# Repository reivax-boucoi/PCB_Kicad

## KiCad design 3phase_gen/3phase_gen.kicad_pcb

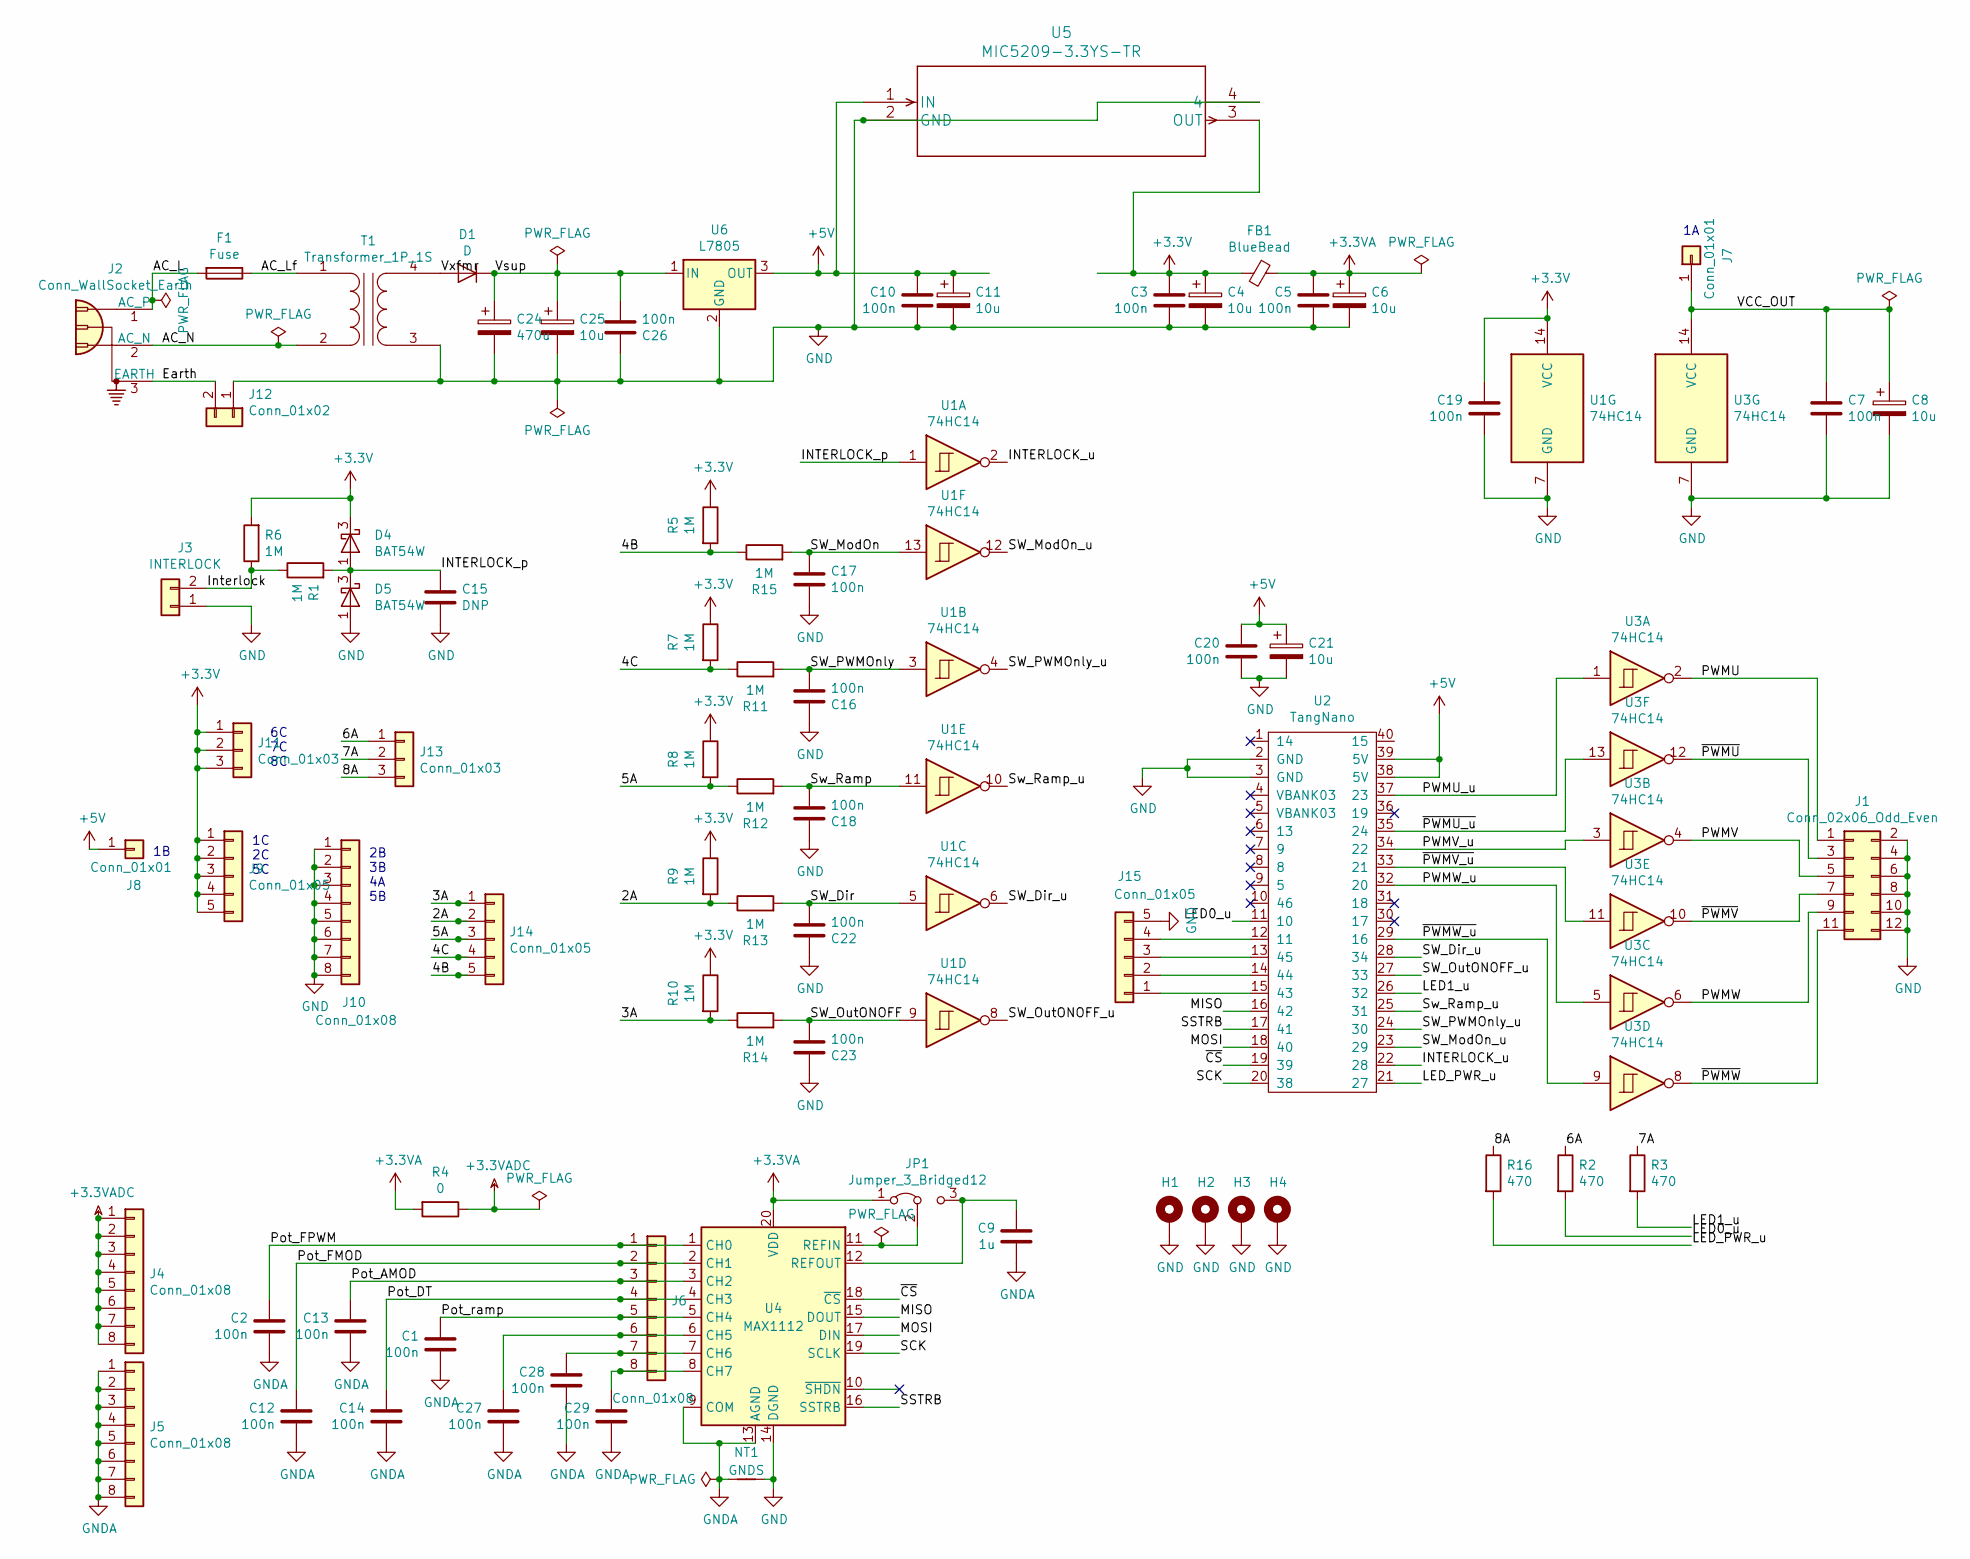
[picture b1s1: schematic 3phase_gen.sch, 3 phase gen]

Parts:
C1, C2, C3, C5, C7, C10, C12, C13, C14, C16, C17, C18, C19, C20, C22, C23, C26, C27, C28, C29: 100n; C_0805_2012Metric_Pad1.15x1.40mm_HandSolder
C4, C6, C8, C11, C21, C25: 10u; CP_Radial_D5.0mm_P2.50mm
C9: 1u; C_0805_2012Metric_Pad1.15x1.40mm_HandSolder
C15: DNP; C_0805_2012Metric_Pad1.15x1.40mm_HandSolder
C24: 470u; CP_Radial_D10.0mm_P5.00mm
D1: D; D_DO-15_P12.70mm_Horizontal
D4, D5: BAT54W; SOT-323_SC-70
F1: Fuse; Fuseholder_Cylinder-5x20mm_Stelvio-Kontek_PTF78_Horizontal_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
FB1: BlueBead; FerriteBead
H1, H2, H3, H4: MountingHole_Pad; MountingHole_3.2mm_M3_Pad
J1: Conn_02x06_Odd_Even; PinHeader_2x06_P2.54mm_Horizontal
J2: Conn_WallSocket_Earth; IEC_mains_3pin
J3: INTERLOCK; SolderWirePad_1x02_P3.81mm_Drill1.2mm
J4, J5, J6, J10: Conn_01x08; PinHeader_1x08_P2.54mm_Vertical
J7, J8: Conn_01x01; PinHeader_1x01_P2.54mm_Vertical
J9, J14, J15: Conn_01x05; PinHeader_1x05_P2.54mm_Vertical
J11, J13: Conn_01x03; PinHeader_1x03_P2.54mm_Vertical
J12: Conn_01x02; PinHeader_1x02_P2.54mm_Vertical
JP1: Jumper_3_Bridged12; SolderJumper-3_P1.3mm_Bridged12_RoundedPad1.0x1.5mm
NT1: GNDS; NetTie-2_SMD_Pad0.5mm
R1, R11, R12, R13, R14, R15: 1M; R_Axial_DIN0207_L6.3mm_D2.5mm_P10.16mm_Horizontal
R2, R3, R16: 470; R_0805_2012Metric_Pad1.15x1.40mm_HandSolder
R4: 0; R_Axial_DIN0207_L6.3mm_D2.5mm_P10.16mm_Horizontal
R5, R6, R7, R8, R9, R10: 1M; R_0805_2012Metric_Pad1.15x1.40mm_HandSolder
T1: Transformer_1P_1S; VB1-2-1-12_transformer
U1, U3: 74HC14; DIP-14_W7.62mm_LongPads
U2: TangNano
U4: MAX1112; SSOP-20_5.3x7.2mm_P0.65mm
U5: MIC5209-3.3YS-TR; SOT-223
U6: L7805; TO-220F-3_Vertical

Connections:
+3.3VA: C5.2, C6.1, FB1.1, JP1.1 (A), R4.2, U4.20 (VDD)
+3.3VADC: J4.1, J4.2, J4.3, J4.4, J4.5, J4.6, J4.7, J4.8, R4.1
+3V3: C3.2, C4.1, C19.2, D4.3 (K), FB1.2, J9.1, J9.2, J9.3, J9.4, J9.5, J11.1, J11.2, J11.3, R5.1, R6.2, R7.1, R8.1, R9.1, R10.1, U1.14 (VCC), U5.3 (OUT)
+5V: C10.2, C11.1, C20.2, C21.1, J8.1, U2.38 (5V), U2.39 (5V), U5.1 (IN), U6.3 (OUT)
/2A: J14.2, R9.2, R13.1
/3A: J14.1, R10.2, R14.1
/4B: J14.5, R5.2, R15.1
/4C: J14.4, R7.2, R11.1
/5A: J14.3, R8.2, R12.1
/6A: J13.1, R2.1
/7A: J13.2, R3.1
/8A: J13.3, R16.1
/AC_L: F1.2, J2.1 (AC_P)
/AC_Lf: F1.1, T1.1 (AA)
/AC_N: J2.2 (AC_N), T1.2 (AB)
/Earth: J2.3 (EARTH), J12.2
/INTERLOCK_p: C15.2, D4.1 (A), D5.3 (K), R1.2, U1.1
/INTERLOCK_u: U1.2, U2.22 (28)
/Interlock: J3.2, R1.1, R6.1
/LED0_u: R2.2, U2.11 (10)
/LED1_u: R3.2, U2.26 (32)
/LED_PWR_u: R16.2, U2.21 (27)
/MISO: U2.16 (42), U4.15 (DOUT)
/MOSI: U2.18 (40), U4.17 (DIN)
/PWMU: J1.1, U3.2
/PWMU_u: U2.37 (23), U3.1
/PWMV: J1.5, U3.4
/PWMV_u: U2.34 (22), U3.3
/PWMW: J1.9, U3.6
/PWMW_u: U2.32 (20), U3.5
/Pot_AMOD: C13.2, J6.3, U4.3 (CH2)
/Pot_DT: C14.2, J6.4, U4.4 (CH3)
/Pot_FMOD: C12.2, J6.2, U4.2 (CH1)
/Pot_FPWM: C2.2, J6.1, U4.1 (CH0)
/Pot_ramp: C1.2, J6.5, U4.5 (CH4)
/SCK: U2.20 (38), U4.19 (SCLK)
/SSTRB: U2.17 (41), U4.16 (SSTRB)
/SW_Dir: C22.1, R13.2, U1.5
/SW_Dir_u: U1.6, U2.28 (34)
/SW_ModOn: C17.2, R15.2, U1.13
/SW_ModOn_u: U1.12, U2.23 (29)
/SW_OutONOFF: C23.1, R14.2, U1.9
/SW_OutONOFF_u: U1.8, U2.27 (33)
/SW_PWMOnly: C16.1, R11.2, U1.3
/SW_PWMOnly_u: U1.4, U2.24 (30)
/Sw_Ramp: C18.1, R12.2, U1.11
/Sw_Ramp_u: U1.10, U2.25 (31)
/VCC_OUT: C7.1, C8.1, J7.1, U3.14 (VCC)
/Vsup: C24.1, C25.1, C26.1, D1.1 (K), U6.1 (IN)
/Vxfmr: D1.2 (A), T1.4 (SB)
/~CS: U2.19 (39), U4.18 (~CS)
/~PWMU: J1.3, U3.12
/~PWMU_u: U2.35 (24), U3.13
/~PWMV: J1.7, U3.10
/~PWMV_u: U2.33 (21), U3.11
/~PWMW: J1.11, U3.8
/~PWMW_u: U2.29 (16), U3.9
GND: C3.1, C4.2, C5.1, C6.2, C7.2, C8.2, C10.1, C11.2, C15.1, C16.2, C17.1, C18.2, C19.1, C20.1, C21.2, C22.2, C23.2, C24.2, C25.2, C26.2, D5.1 (A), H1.1, H2.1, H3.1, H4.1, J1.2, J1.4, J1.6, J1.8, J1.10, J1.12, J3.1, J10.1, J10.2, J10.3, J10.4, J10.5, J10.6, J10.7, J10.8, J12.1, J15.5, NT1.2, T1.3 (SA), U1.7 (GND), U2.2 (GND), U2.3 (GND), U3.7 (GND), U4.14 (DGND), U5.2 (GND), U5.4, U6.2 (GND)
GNDA: C1.1, C2.1, C9.1, C12.1, C13.1, C14.1, C27.1, C28.1, C29.1, J5.1, J5.2, J5.3, J5.4, J5.5, J5.6, J5.7, J5.8, NT1.1, U4.9 (COM), U4.13 (AGND)
unnamed: C9.2, JP1.3 (B), U4.12 (REFOUT)
unnamed: C27.2, J6.6, U4.6 (CH5)
unnamed: C28.2, J6.7, U4.7 (CH6)
unnamed: C29.2, J6.8, U4.8 (CH7)
unnamed: J15.1, U2.15 (43)
unnamed: J15.2, U2.14 (44)
unnamed: J15.3, U2.13 (45)
unnamed: J15.4, U2.12 (11)
unnamed: JP1.2 (C), U4.11 (REFIN)

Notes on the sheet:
1C 2C 5C
2B 3B 4A 5B
6C 7C 8C

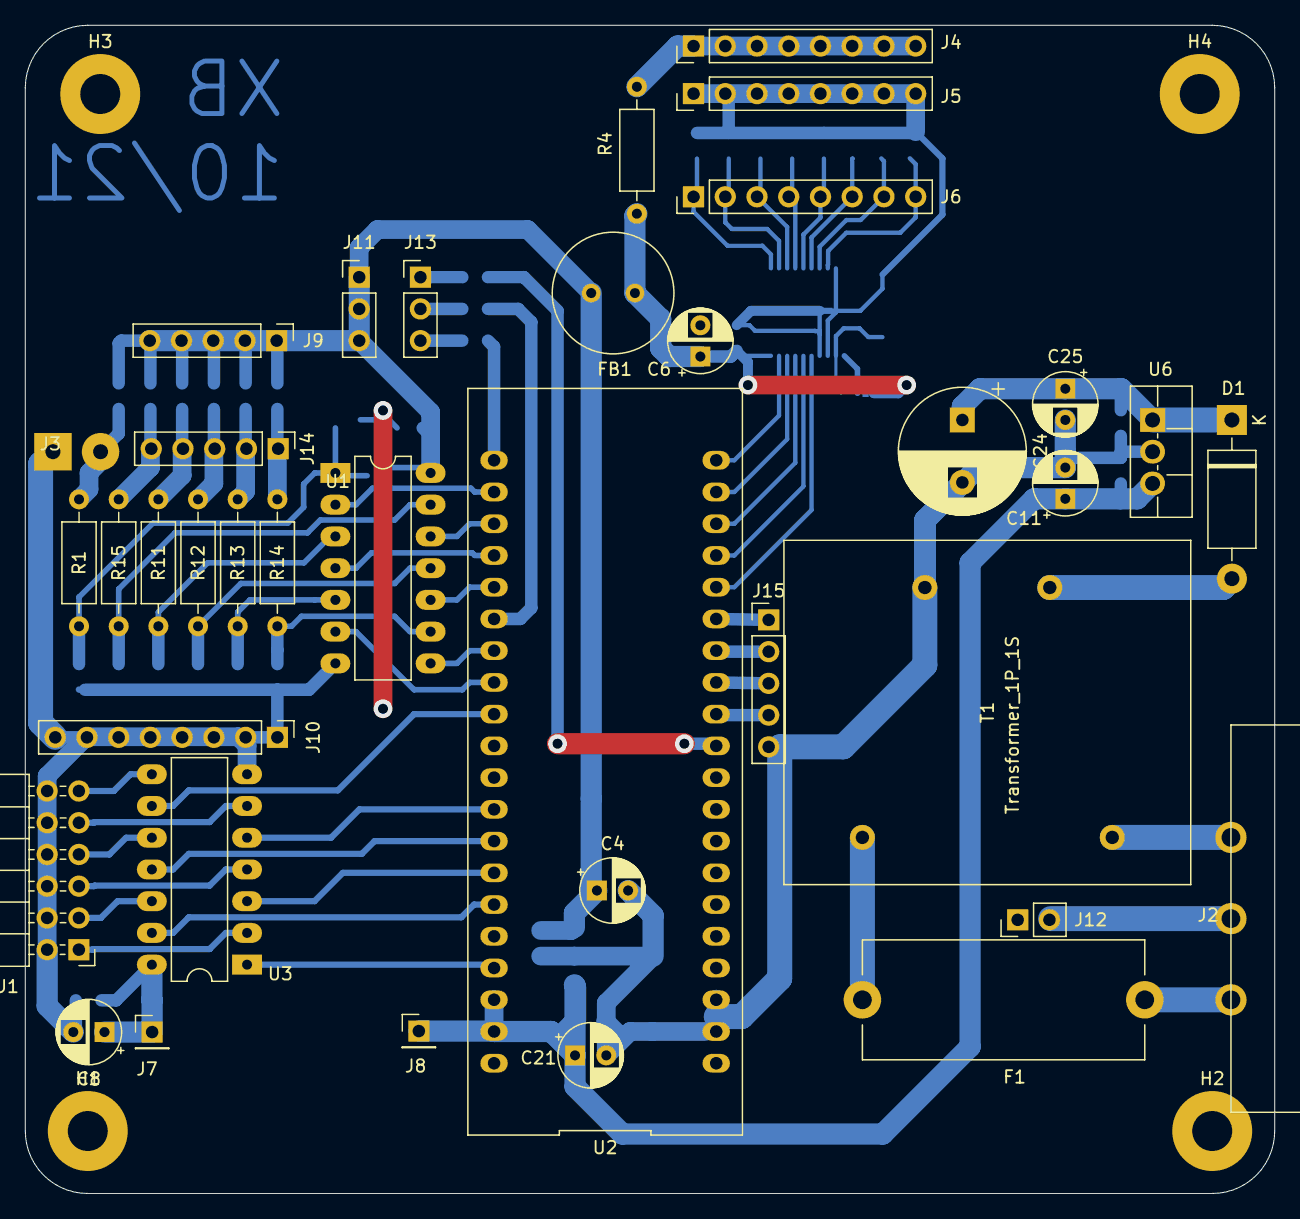
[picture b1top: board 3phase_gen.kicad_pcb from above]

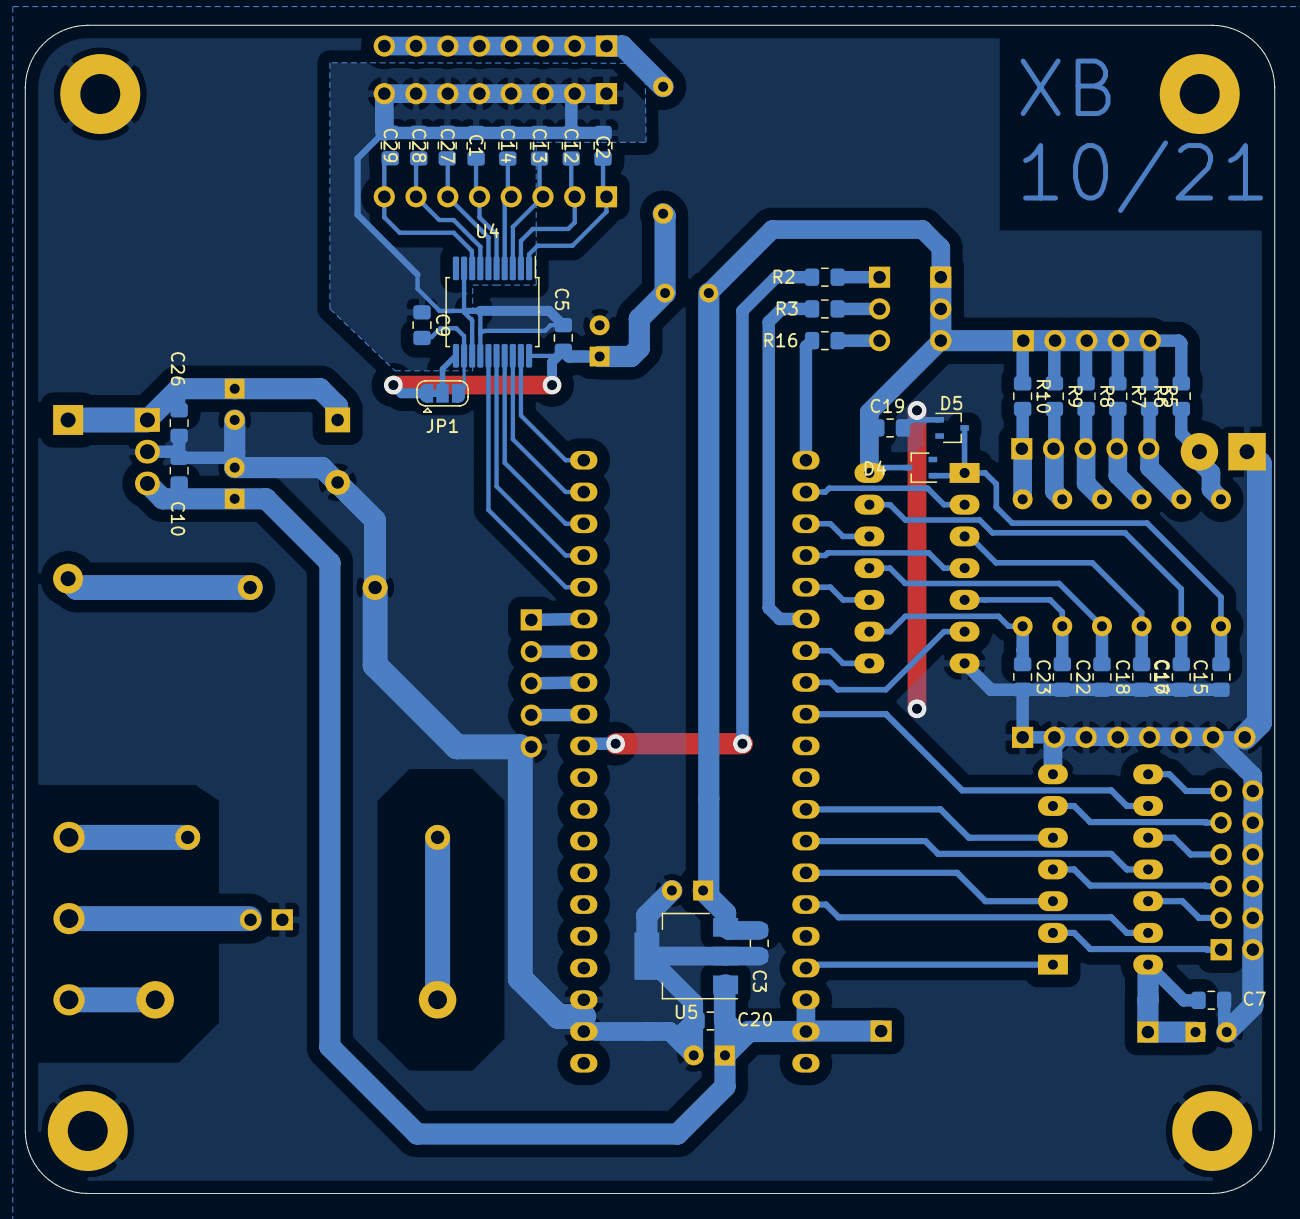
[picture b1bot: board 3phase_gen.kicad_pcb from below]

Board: 2 copper layers, 100.0 x 93.5 mm, 78 parts (37 on the bottom side), 68 nets.

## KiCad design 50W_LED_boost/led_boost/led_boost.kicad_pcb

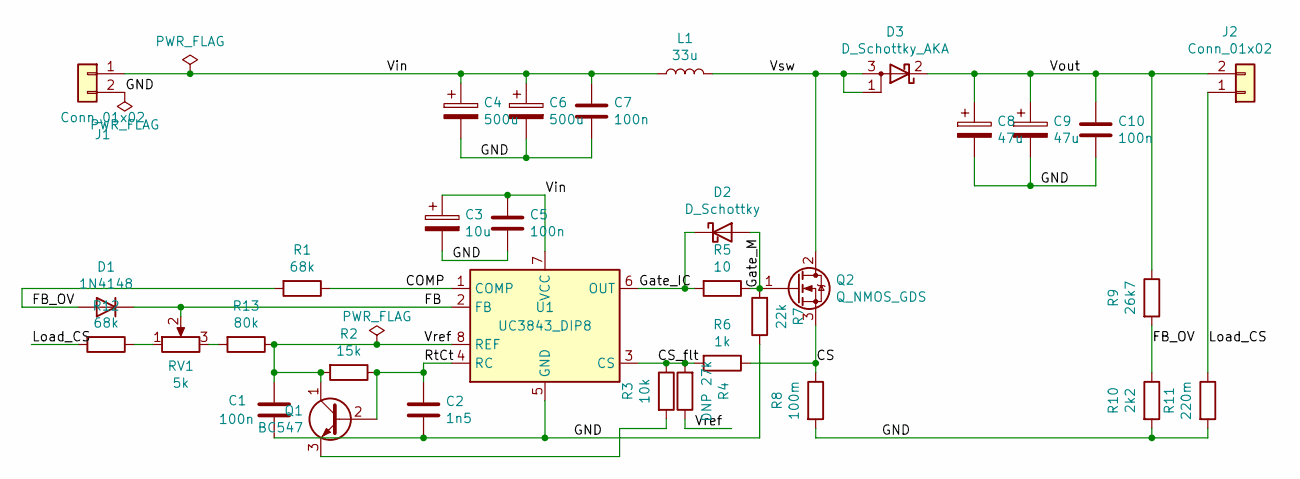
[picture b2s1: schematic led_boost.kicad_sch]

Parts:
C1, C5, C7, C10: 100n; C_Disc_D5.0mm_W2.5mm_P5.00mm
C2: 1n5; C_Disc_D5.0mm_W2.5mm_P5.00mm
C3: 10u; CP_Radial_D10.0mm_P5.00mm
C4, C6: 500u; CP_Radial_D13.0mm_P7.50mm
C8, C9: 47u; CP_Radial_D10.0mm_P5.00mm
D1: 1N4148; D_DO-35_SOD27_P7.62mm_Horizontal
D2: D_Schottky; D_DO-15_P12.70mm_Horizontal
D3: D_Schottky_AKA; TO-220-3_Vertical
J1, J2: Conn_01x02; TE_826576-2_1x02_P3.96mm_Vertical
L1: 33u; L_Radial_D12.5mm_P7.00mm_Fastron_09HCP
Q1: BC547; TO-92_Inline
Q2: Q_NMOS_GDS; TO-220-3_Vertical
R1, R12: 68k; R_Axial_DIN0207_L6.3mm_D2.5mm_P10.16mm_Horizontal
R2: 15k; R_Axial_DIN0207_L6.3mm_D2.5mm_P10.16mm_Horizontal
R3: 10k; R_Axial_DIN0207_L6.3mm_D2.5mm_P10.16mm_Horizontal
R4: DNP 27k; R_Axial_DIN0207_L6.3mm_D2.5mm_P10.16mm_Horizontal
R5: 10; R_Axial_DIN0207_L6.3mm_D2.5mm_P10.16mm_Horizontal
R6: 1k; R_Axial_DIN0207_L6.3mm_D2.5mm_P10.16mm_Horizontal
R7: 22k; R_Axial_DIN0207_L6.3mm_D2.5mm_P10.16mm_Horizontal
R8: 100m; R_Shunt_Vishay_WSR2_WSR3_KelvinConnection
R9: 26k7; R_Axial_DIN0207_L6.3mm_D2.5mm_P10.16mm_Horizontal
R10: 2k2; R_Axial_DIN0207_L6.3mm_D2.5mm_P10.16mm_Horizontal
R11: 220m; R_Radial_Power_L7.0mm_W8.0mm_Px2.40mm_Py2.30mm
R13: 80k; R_Axial_DIN0207_L6.3mm_D2.5mm_P10.16mm_Horizontal
RV1: 5k; Potentiometer_Bourns_3296X_Horizontal
U1: UC3843_DIP8; DIP-8_W7.62mm

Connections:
/COMP: R1.1, U1.1 (COMP)
/CS: Q2.3 (S), R6.1, R8.1
/CS_flt: R3.1, R4.2, R6.2, U1.3 (CS)
/FB: D1.1 (K), RV1.2, U1.2 (FB)
/FB_OV: D1.2 (A), R1.2, R9.2, R10.1
/GND: C1.2, C2.2, C3.2, C4.2, C5.2, C6.2, C7.2, C8.2, C9.2, C10.2, J1.2, R7.1, R8.2, R10.2, R11.2, U1.5 (GND)
/Gate_IC: D2.1 (K), R5.2, U1.6 (OUT)
/Gate_M: D2.2 (A), Q2.1 (G), R5.1, R7.2
/Load_CS: J2.1, R11.1, R12.2
/RtCt: C2.1, Q1.2 (B), R2.1, U1.4 (RC)
/Vin: C3.1, C4.1, C5.1, C6.1, C7.1, J1.1, L1.1, U1.7 (VCC)
/Vout: C8.1, C9.1, C10.1, D3.2 (K), J2.2, R9.1
/Vref: C1.1, Q1.1 (C), R2.2, R4.1, R13.1, U1.8 (REF)
/Vsw: D3.1 (A), D3.3 (A), L1.2, Q2.2 (D)
unnamed: Q1.3 (E), R3.2
unnamed: R12.1, RV1.1
unnamed: R13.2, RV1.3

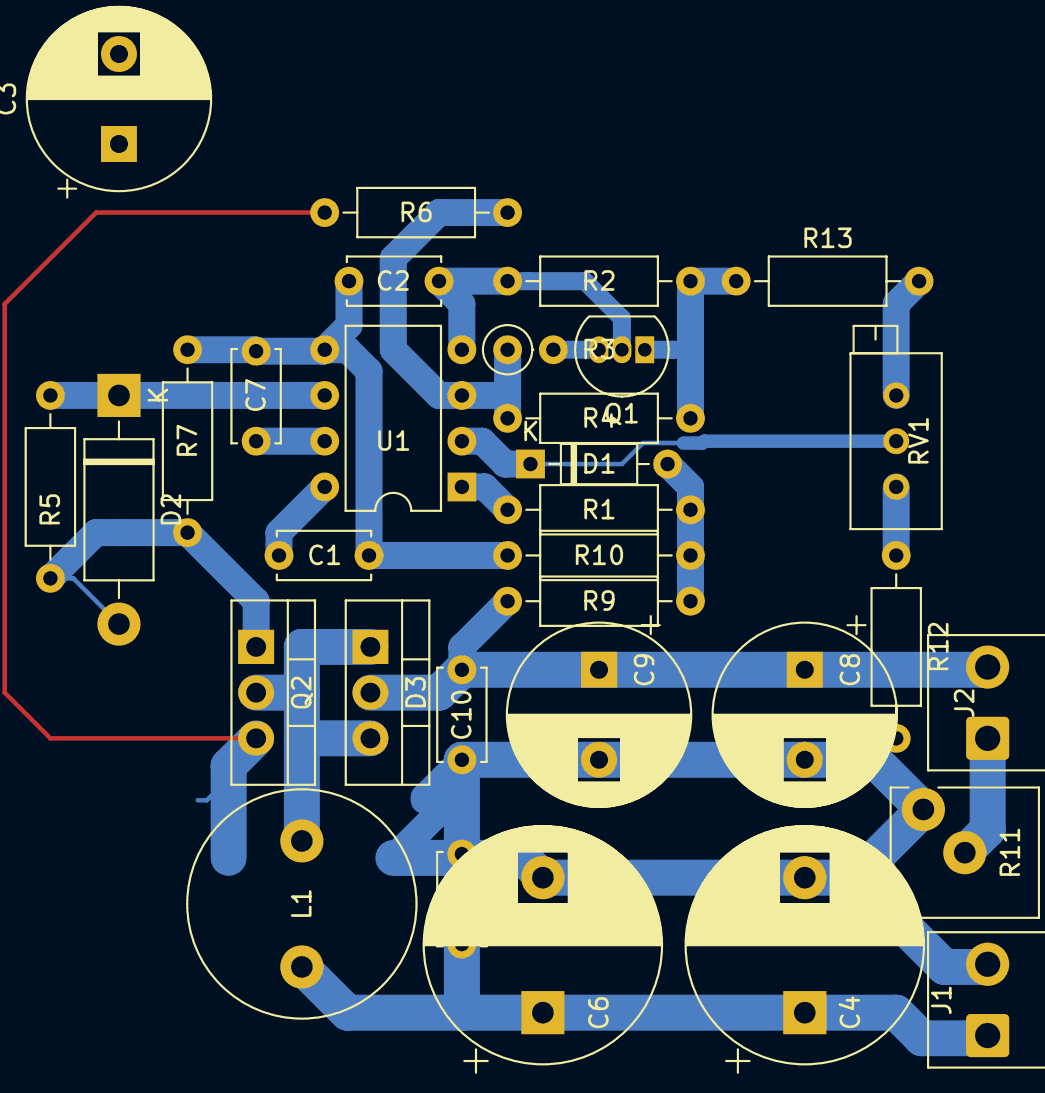
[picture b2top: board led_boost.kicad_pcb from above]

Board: 2 copper layers, 33 parts (1 on the bottom side), 17 nets.

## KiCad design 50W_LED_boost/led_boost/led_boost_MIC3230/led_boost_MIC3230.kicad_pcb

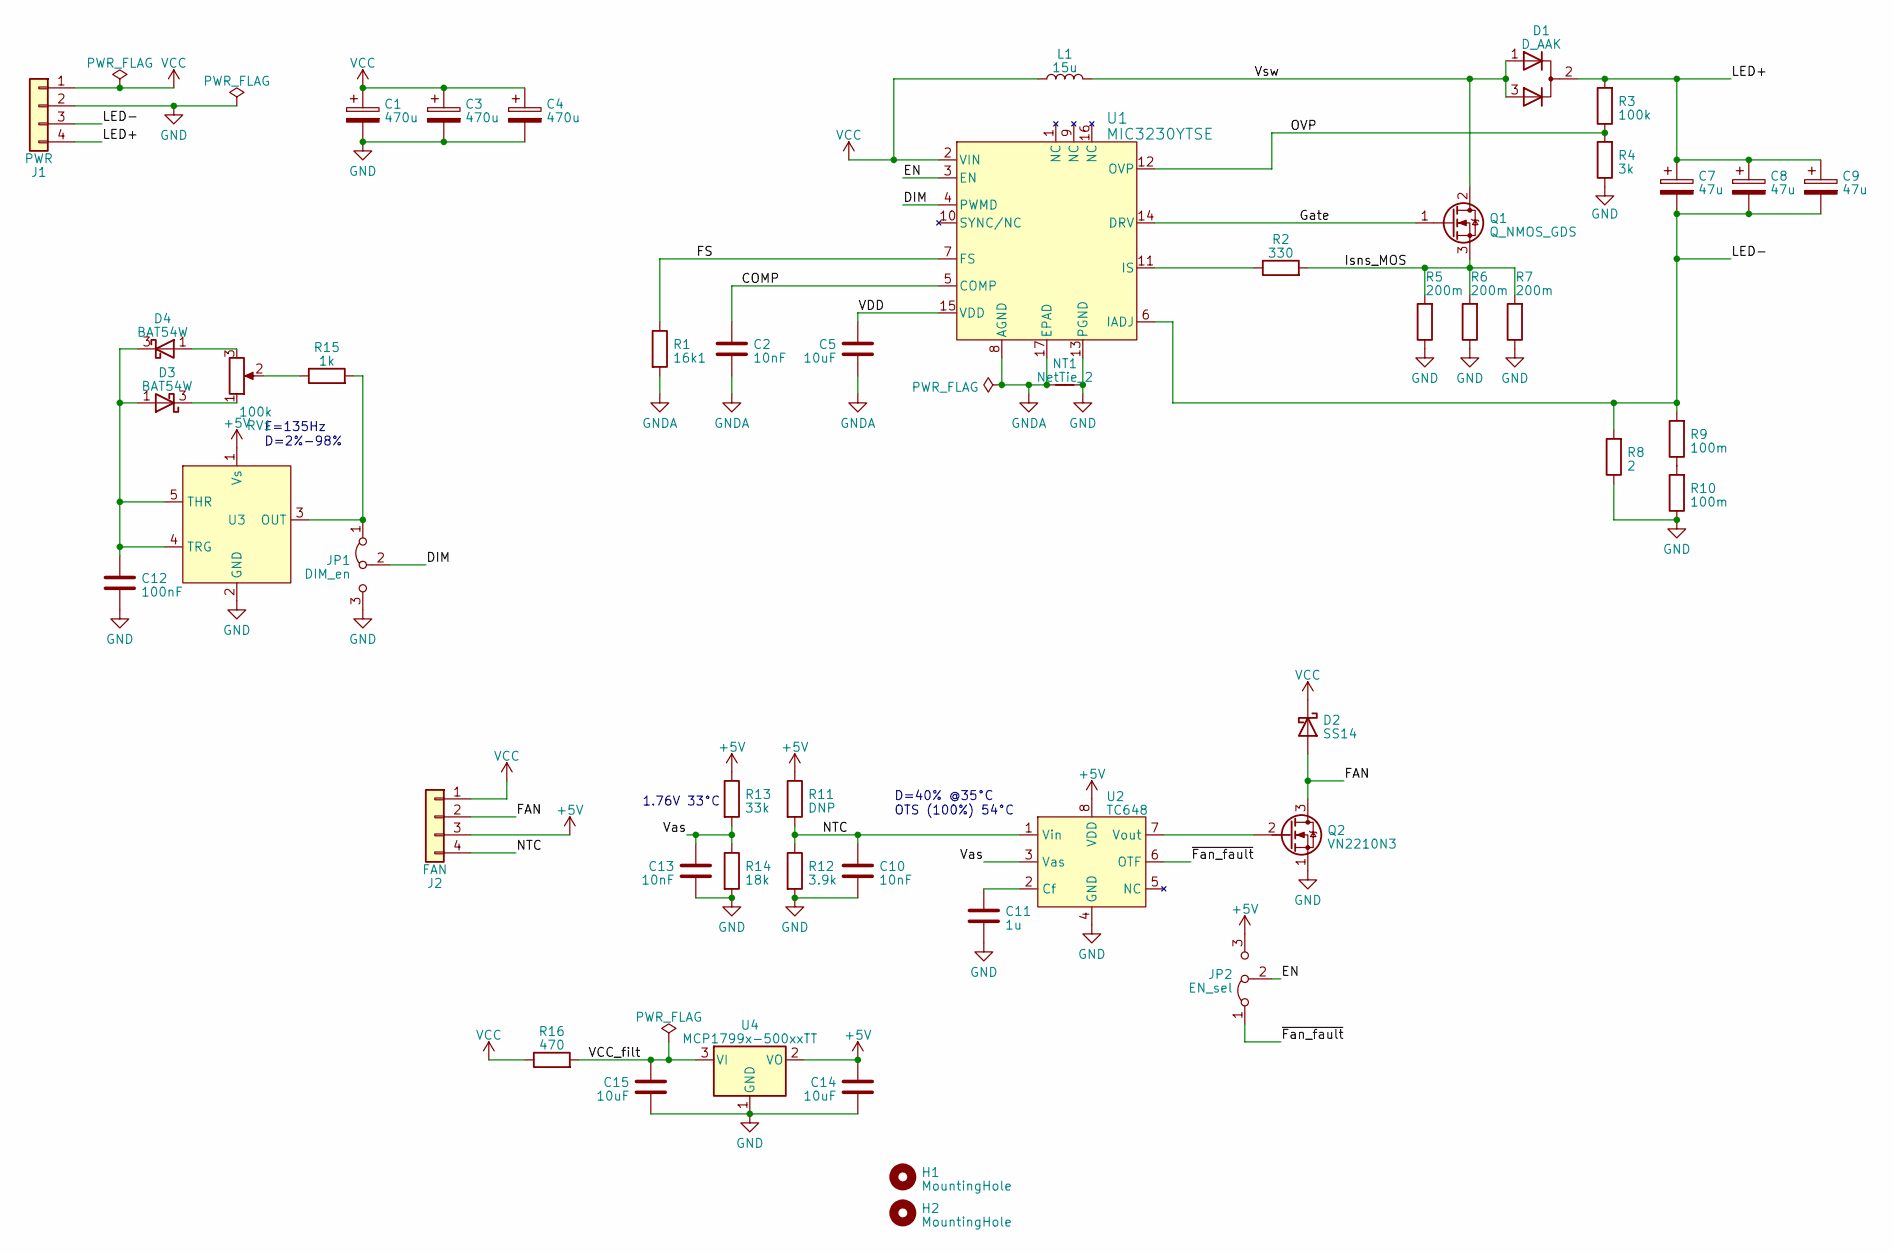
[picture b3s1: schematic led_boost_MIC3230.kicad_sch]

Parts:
C1, C3, C4: 470u; CP_Radial_D10.0mm_P5.00mm
C2, C10, C13: 10nF; C_0805_2012Metric_Pad1.18x1.45mm_HandSolder
C5, C14, C15: 10uF; C_0805_2012Metric_Pad1.18x1.45mm_HandSolder
C7, C8, C9: 47u; CP_Radial_D7.5mm_P2.50mm
C11: 1u; C_0805_2012Metric_Pad1.18x1.45mm_HandSolder
C12: 100nF; C_0805_2012Metric_Pad1.18x1.45mm_HandSolder
D1: D_AAK; TO-220-3_Vertical
D2: SS14; D_SMA
D3, D4: BAT54W; SOT-323_SC-70
H1, H2: MountingHole; MountingHole_3.2mm_M3
J1: PWR; 1986712-4_TE_Connectivity
J2: FAN; PinHeader_1x04_P2.54mm_Vertical
JP1: DIM_en; SolderJumper-3_P1.3mm_Bridged12_RoundedPad1.0x1.5mm
JP2: EN_sel; SolderJumper-3_P1.3mm_Bridged12_RoundedPad1.0x1.5mm
L1: 15u; PCV-1-153-10L
NT1: NetTie_2; NetTie-2_SMD_Pad0.5mm
Q1: Q_NMOS_GDS; TO-220-3_Vertical
Q2: VN2210N3; TO-92L_HandSolder
R1: 16k1; R_0603_1608Metric_Pad0.98x0.95mm_HandSolder
R2: 330; R_0603_1608Metric_Pad0.98x0.95mm_HandSolder
R3: 100k; R_0603_1608Metric_Pad0.98x0.95mm_HandSolder
R4: 3k; R_0603_1608Metric_Pad0.98x0.95mm_HandSolder
R5, R6, R7: 200m; R_2512_6332Metric
R8: 2; R_1210_3225Metric
R9, R10: 100m; R_1210_3225Metric
R11: DNP; R_0603_1608Metric_Pad0.98x0.95mm_HandSolder
R12: 3.9k; R_0603_1608Metric_Pad0.98x0.95mm_HandSolder
R13: 33k; R_0603_1608Metric_Pad0.98x0.95mm_HandSolder
R14: 18k; R_0603_1608Metric_Pad0.98x0.95mm_HandSolder
R15: 1k; R_0603_1608Metric_Pad0.98x0.95mm_HandSolder
R16: 470; R_0805_2012Metric
RV1: 100k; Potentiometer_oldTV_greyKnob
U1: MIC3230YTSE; TSSOP-16-1EP_4.4x5mm_P0.65mm
U2: TC648; SOIC-8_3.9x4.9mm_P1.27mm
U3: SOT-23-5_HandSoldering
U4: MCP1799x-500xxTT; SOT-23

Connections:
+5V: C14.1, J2.3, JP2.3 (B), R11.1, R13.1, U2.8 (VDD), U3.1 (Vs), U4.2 (VO)
/COMP: C2.1, U1.5 (COMP)
/DIM: JP1.2 (C), U1.4 (PWMD)
/EN: JP2.2 (C), U1.3 (EN)
/FAN: D2.2 (A), J2.2, Q2.3 (D)
/FS: R1.1, U1.7 (FS)
/Gate: Q1.1 (G), U1.14 (DRV)
/Isns_MOS: Q1.3 (S), R2.2, R5.2, R6.2, R7.2
/LED+: C7.1, C8.1, C9.1, D1.2 (A), J1.4, R3.2
/LED-: C7.2, C8.2, C9.2, J1.3, R8.2, R9.2, U1.6 (IADJ)
/NTC: C10.1, J2.4, R11.2, R12.1, U2.1 (Vin)
/OVP: R3.1, R4.2, U1.12 (OVP)
/VCC_filt: C15.1, R16.2, U4.3 (VI)
/VDD: C5.1, U1.15 (VDD)
/Vas: C13.1, R13.2, R14.1, U2.3 (Vas)
/Vsw: D1.1 (K), D1.3 (K), L1.2, Q1.2 (D)
/~Fan_fault: JP2.1 (A), U2.6 (OTF)
GND: C1.2, C3.2, C4.2, C10.2, C11.2, C12.2, C13.2, C14.2, C15.2, J1.2, JP1.3 (B), NT1.2, Q2.1 (S), R4.1, R5.1, R6.1, R7.1, R8.1, R10.1, R12.2, R14.2, U1.13 (PGND), U2.4 (GND), U3.2 (GND), U4.1 (GND)
GNDA: C2.2, C5.2, NT1.1, R1.2, U1.8 (AGND), U1.17 (EPAD)
unnamed: C12.1, D3.1 (A), D4.3 (K), U3.4 (TRG), U3.5 (THR)
unnamed: D3.3 (K), RV1.1
unnamed: D4.1 (A), RV1.3
unnamed: JP1.1 (A), R15.2, U3.3 (OUT)
unnamed: Q2.2 (G), U2.7 (Vout)
unnamed: R9.1, R10.2
unnamed: R15.1, RV1.2
unnamed: R2.1, U1.11 (IS)
unnamed: C11.1, U2.2 (Cf)
VCC: C1.1, C3.1, C4.1, D2.1 (K), J1.1, J2.1, L1.1, R16.1, U1.2 (VIN)

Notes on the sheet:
F=135Hz D=2%-98%
D=40% @35°C OTS (100%) 54°C
1.76V 33°C

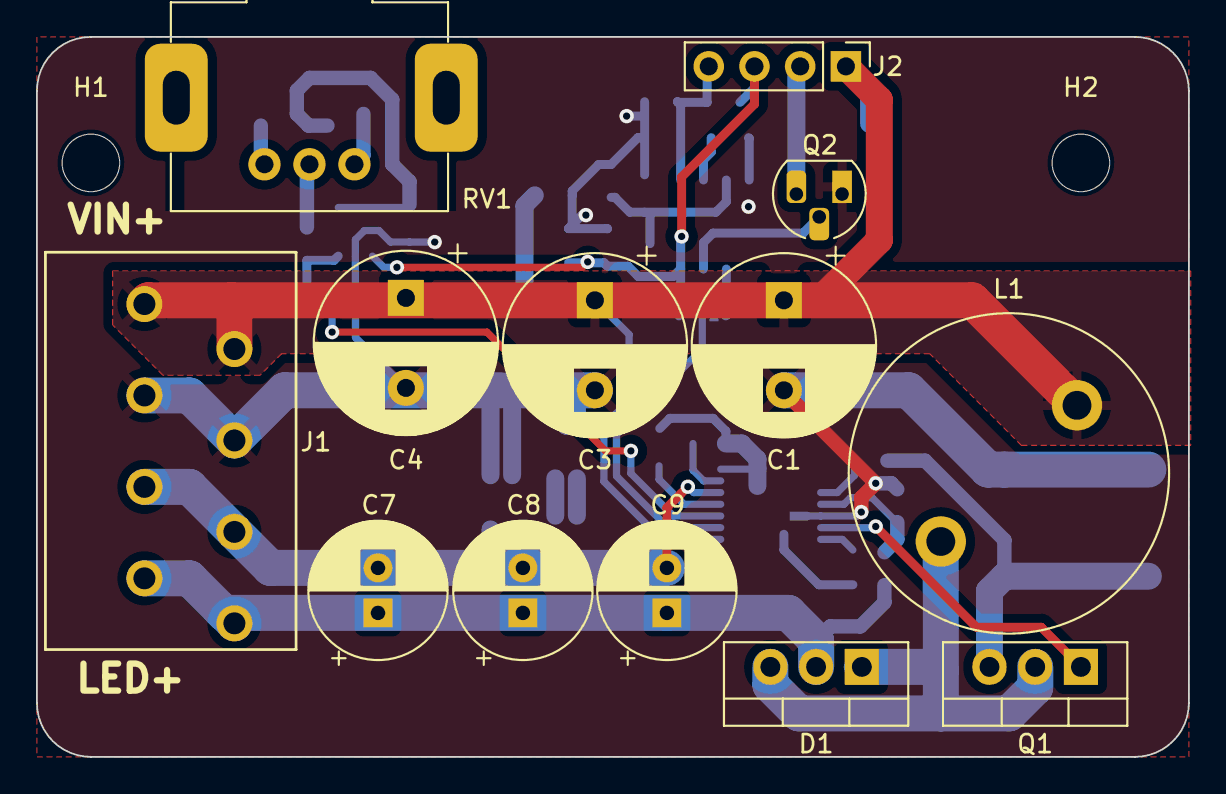
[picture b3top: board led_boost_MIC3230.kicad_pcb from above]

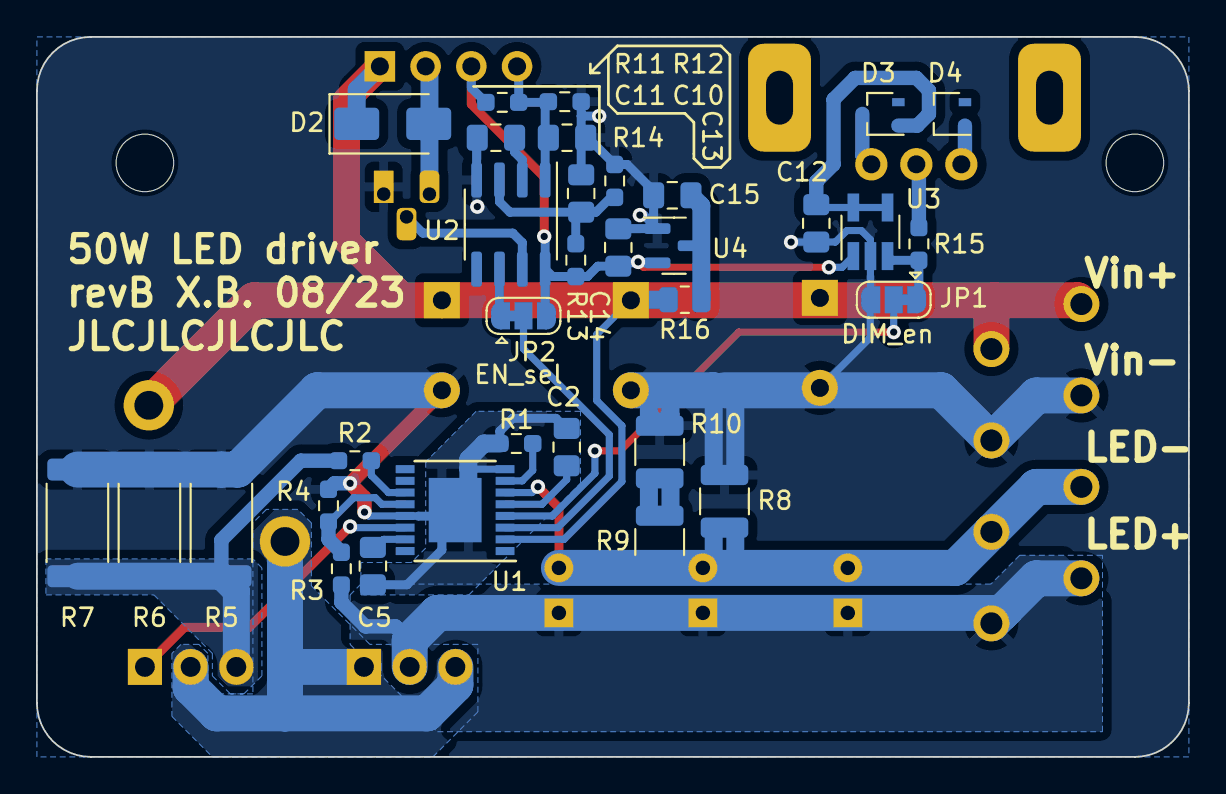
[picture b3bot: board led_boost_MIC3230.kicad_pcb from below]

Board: 2 copper layers, 64.0 x 40.0 mm, 49 parts (34 on the bottom side), 29 nets.
